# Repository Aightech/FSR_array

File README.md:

# FSR_array

This project implements a electronic skin using a FSR accelerometers arrays. 

The electronic board uses two multiplexers and two 16-channel ADCs to read the FSRs. The multiplexers are used to select the row or column of the FSRs array. The ADCs are used to read the FSRs values.
A teensy 4.1 is used to control the multiplexers and ADCs and to send the data to the computer.
The teensy 4.1 is connected to the computer using a USB cable or ethernet cable.
There are two modes of operation:
- **Single mode**: In this mode, you can connect a FSR array with up to 32x32 FSRs.
- **Dual mode**: In this mode, you can connect two FSR arrays with up to 16x16 FSRs each.

The sampling is around 400KHz/channel. So for a 16x16 FSR array, the sampling rate is around 400KHz/256 = 1562.5Hz.

The project contains a C++/matlab/python code demonstrating how to communicate with the teensy 4.1 and read the FSRs values.

### Submodules dependencies
#### libraries
- [built_lsl](lib/built_lsl/README.md)
- [com_client](lib/com_client/README.md)

# Building source code

To build the project run:
```bash
cd FSR_array
mkdir build && cd build
cmake .. && make
```

# Demonstration app

When the project have been built, you can run:
```bash
./FSR_array -h
```
to get the demonstration app usage.

# Example
Open the  file to get an example how to use the lib.

# Contributing
See [CONTRIBUTING.md](CONTRIBUTING.md) for details on our code of conduct, and the process for submitting pull requests to us.

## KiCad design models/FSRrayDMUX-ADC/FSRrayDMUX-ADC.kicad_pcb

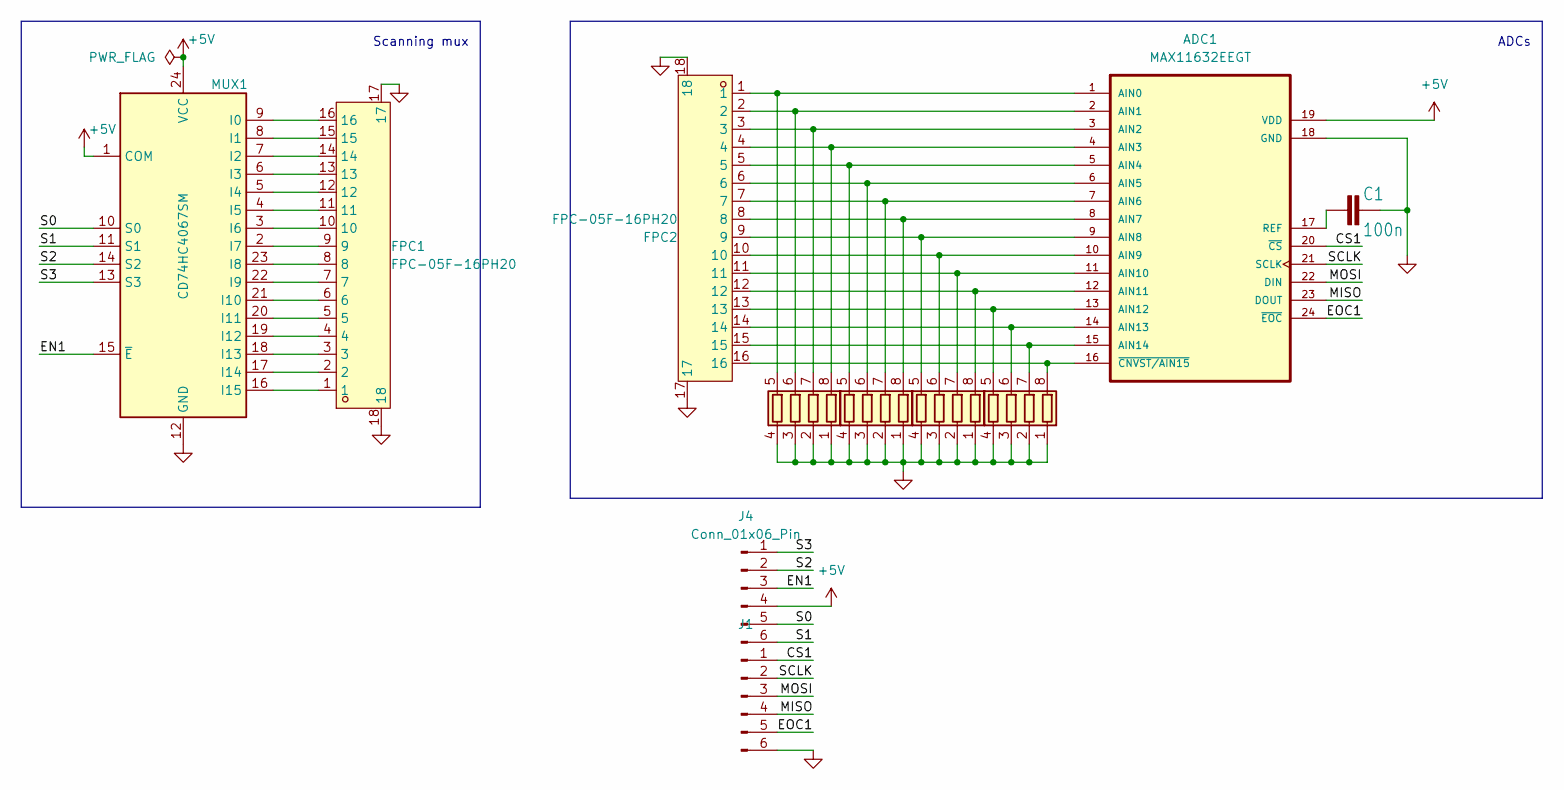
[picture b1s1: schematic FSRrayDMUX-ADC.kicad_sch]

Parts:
ADC1: MAX11632EEGT
C1: 100n; C_0402_1005Metric
FPC1, FPC2: FPC-05F-16PH20; FPC-SMD_16P-P0.50_FPC-05F-16PH20; LCSC Part C2856801
J1, J4: Conn_01x06_Pin; PinSocket_1x06_P2.54mm_Vertical
MUX1: CD74HC4067SM; SSOP-24_5.3x8.2mm_P0.65mm
RN1, RN2, RN3, RN4: R_Pack04; R_Array_Convex_4x0402

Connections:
+5V: ADC1.19 (VDD), J4.4, MUX1.1 (COM), MUX1.24 (VCC)
/CS1: ADC1.20 (~CS), J1.1
/EN1: J4.3, MUX1.15 (~E)
/EOC1: ADC1.24 (~EOC), J1.5
/MISO: ADC1.23 (DOUT), J1.4
/MOSI: ADC1.22 (DIN), J1.3
/S0: J4.5, MUX1.10 (S0)
/S1: J4.6, MUX1.11 (S1)
/S2: J4.2, MUX1.14 (S2)
/S3: J4.1, MUX1.13 (S3)
/SCLK: ADC1.21 (SCLK), J1.2
GND: ADC1.18 (GND), C1.2, FPC1.17, FPC1.18, FPC2.17, FPC2.18, J1.6, MUX1.12 (GND), RN1.1 (R1.1), RN1.2 (R2.1), RN1.3 (R3.1), RN1.4 (R4.1), RN2.1 (R1.1), RN2.2 (R2.1), RN2.3 (R3.1), RN2.4 (R4.1), RN3.1 (R1.1), RN3.2 (R2.1), RN3.3 (R3.1), RN3.4 (R4.1), RN4.1 (R1.1), RN4.2 (R2.1), RN4.3 (R3.1), RN4.4 (R4.1)
unnamed: ADC1.1 (AIN0), FPC2.1, RN1.5 (R4.2)
unnamed: ADC1.2 (AIN1), FPC2.2, RN1.6 (R3.2)
unnamed: ADC1.3 (AIN2), FPC2.3, RN1.7 (R2.2)
unnamed: ADC1.4 (AIN3), FPC2.4, RN1.8 (R1.2)
unnamed: ADC1.5 (AIN4), FPC2.5, RN2.5 (R4.2)
unnamed: ADC1.6 (AIN5), FPC2.6, RN2.6 (R3.2)
unnamed: ADC1.7 (AIN6), FPC2.7, RN2.7 (R2.2)
unnamed: ADC1.8 (AIN7), FPC2.8, RN2.8 (R1.2)
unnamed: ADC1.9 (AIN8), FPC2.9, RN3.5 (R4.2)
unnamed: ADC1.10 (AIN9), FPC2.10, RN3.6 (R3.2)
unnamed: ADC1.11 (AIN10), FPC2.11, RN3.7 (R2.2)
unnamed: ADC1.12 (AIN11), FPC2.12, RN3.8 (R1.2)
unnamed: ADC1.13 (AIN12), FPC2.13, RN4.5 (R4.2)
unnamed: ADC1.14 (AIN13), FPC2.14, RN4.6 (R3.2)
unnamed: ADC1.15 (AIN14), FPC2.15, RN4.7 (R2.2)
unnamed: ADC1.17 (REF), C1.1
unnamed: ADC1.16 (~CNVST/AIN15), FPC2.16, RN4.8 (R1.2)
unnamed: FPC1.16, MUX1.9 (I0)
unnamed: FPC1.15, MUX1.8 (I1)
unnamed: FPC1.14, MUX1.7 (I2)
unnamed: FPC1.13, MUX1.6 (I3)
unnamed: FPC1.12, MUX1.5 (I4)
unnamed: FPC1.11, MUX1.4 (I5)
unnamed: FPC1.10, MUX1.3 (I6)
unnamed: FPC1.9, MUX1.2 (I7)
unnamed: FPC1.8, MUX1.23 (I8)
unnamed: FPC1.7, MUX1.22 (I9)
unnamed: FPC1.6, MUX1.21 (I10)
unnamed: FPC1.5, MUX1.20 (I11)
unnamed: FPC1.4, MUX1.19 (I12)
unnamed: FPC1.3, MUX1.18 (I13)
unnamed: FPC1.2, MUX1.17 (I14)
unnamed: FPC1.1, MUX1.16 (I15)

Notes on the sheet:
ADCs
Scanning mux

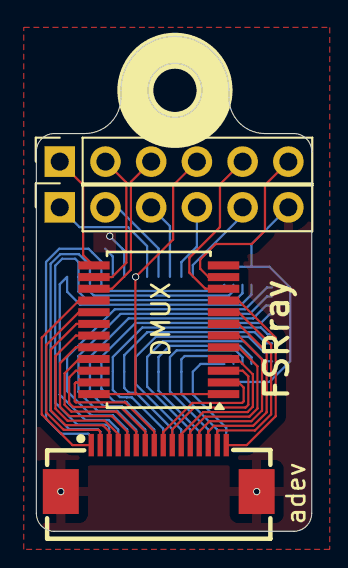
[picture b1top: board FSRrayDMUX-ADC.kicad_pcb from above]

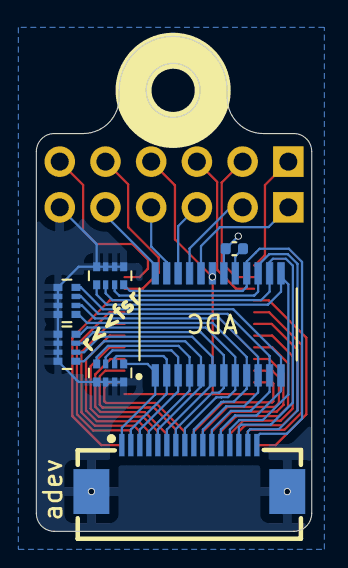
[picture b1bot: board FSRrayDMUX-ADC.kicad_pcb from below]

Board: 4 copper layers, 15.3 x 27.5 mm, 11 parts (7 on the bottom side), 45 nets.

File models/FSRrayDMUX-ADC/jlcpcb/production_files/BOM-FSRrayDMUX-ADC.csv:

Comment,Designator,Footprint,LCSC,Quantity
FPC-05F-16PH20,"FPC1,FPC2",FPC-SMD_16P-P0.50_FPC-05F-16PH20,C2856801,2
Conn_01x06_Pin,J1,PinSocket_1x06_P2.54mm_Vertical,,1
CD74HC4067SM,MUX1,SSOP-24_5.3x8.2mm_P0.65mm,,1
Conn_01x06_Pin,J4,PinSocket_1x06_P2.54mm_Vertical,,1
R_Pack04,RN4,R_Array_Convex_4x0402,,1
R_Pack04,RN2,R_Array_Convex_4x0402,,1
R_Pack04,RN1,R_Array_Convex_4x0402,,1
100n,C1,C_0402_1005Metric,,1
R_Pack04,RN3,R_Array_Convex_4x0402,,1
MAX11632EEGT,ADC1,MAX11632EEGT,,1

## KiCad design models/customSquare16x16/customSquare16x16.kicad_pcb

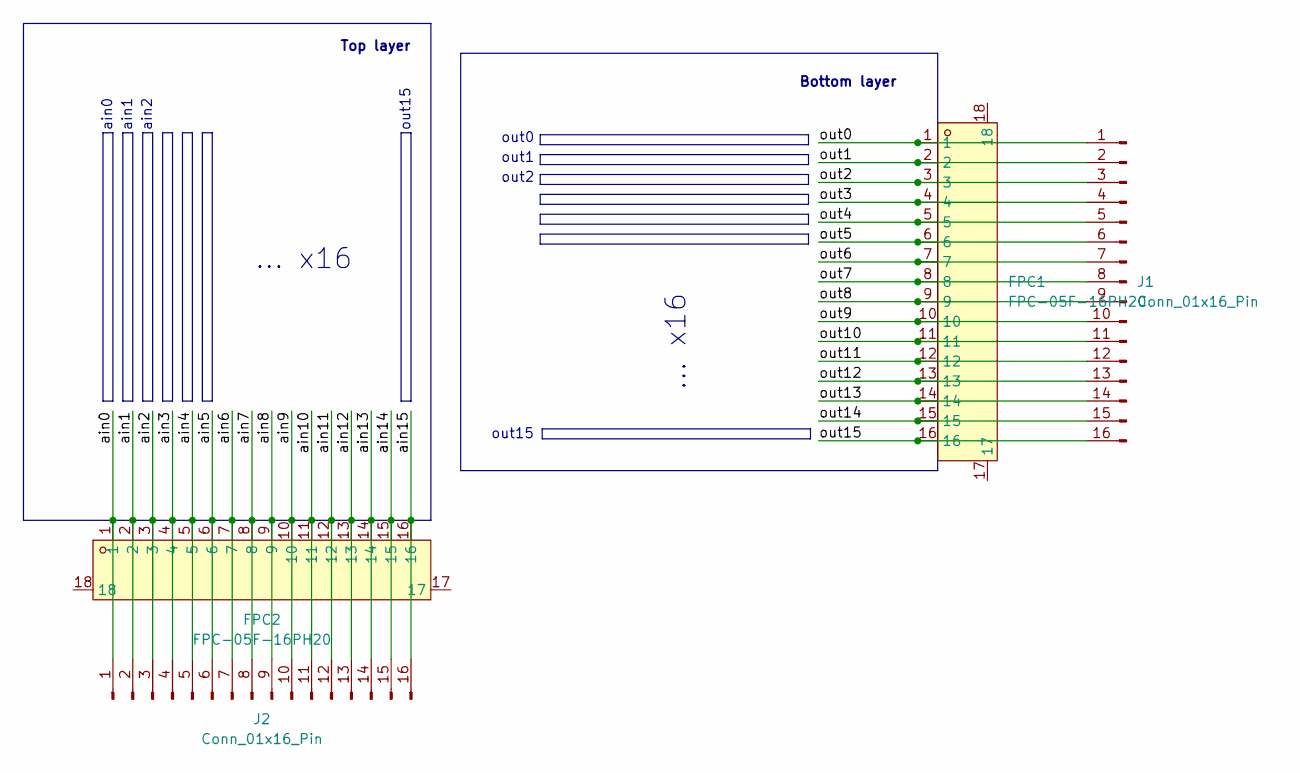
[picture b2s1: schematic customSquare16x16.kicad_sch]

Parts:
FPC1, FPC2: FPC-05F-16PH20; FPC-SMD_16P-P0.50_FPC-05F-16PH20; LCSC Part C2856801
J1, J2: Conn_01x16_Pin; PinSocket_1x16_P2.54mm_Vertical

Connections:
/ain0: FPC2.1, J2.1
/ain1: FPC2.2, J2.2
/ain2: FPC2.3, J2.3
/ain3: FPC2.4, J2.4
/ain4: FPC2.5, J2.5
/ain5: FPC2.6, J2.6
/ain6: FPC2.7, J2.7
/ain7: FPC2.8, J2.8
/ain8: FPC2.9, J2.9
/ain9: FPC2.10, J2.10
/ain10: FPC2.11, J2.11
/ain11: FPC2.12, J2.12
/ain12: FPC2.13, J2.13
/ain13: FPC2.14, J2.14
/ain14: FPC2.15, J2.15
/ain15: FPC2.16, J2.16
/out0: FPC1.1, J1.1
/out1: FPC1.2, J1.2
/out2: FPC1.3, J1.3
/out3: FPC1.4, J1.4
/out4: FPC1.5, J1.5
/out5: FPC1.6, J1.6
/out6: FPC1.7, J1.7
/out7: FPC1.8, J1.8
/out8: FPC1.9, J1.9
/out9: FPC1.10, J1.10
/out10: FPC1.11, J1.11
/out11: FPC1.12, J1.12
/out12: FPC1.13, J1.13
/out13: FPC1.14, J1.14
/out14: FPC1.15, J1.15
/out15: FPC1.16, J1.16

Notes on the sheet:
... x16
Bottom layer
ain0
out15
ain1
Top layer
ain2
out2
out0
out1

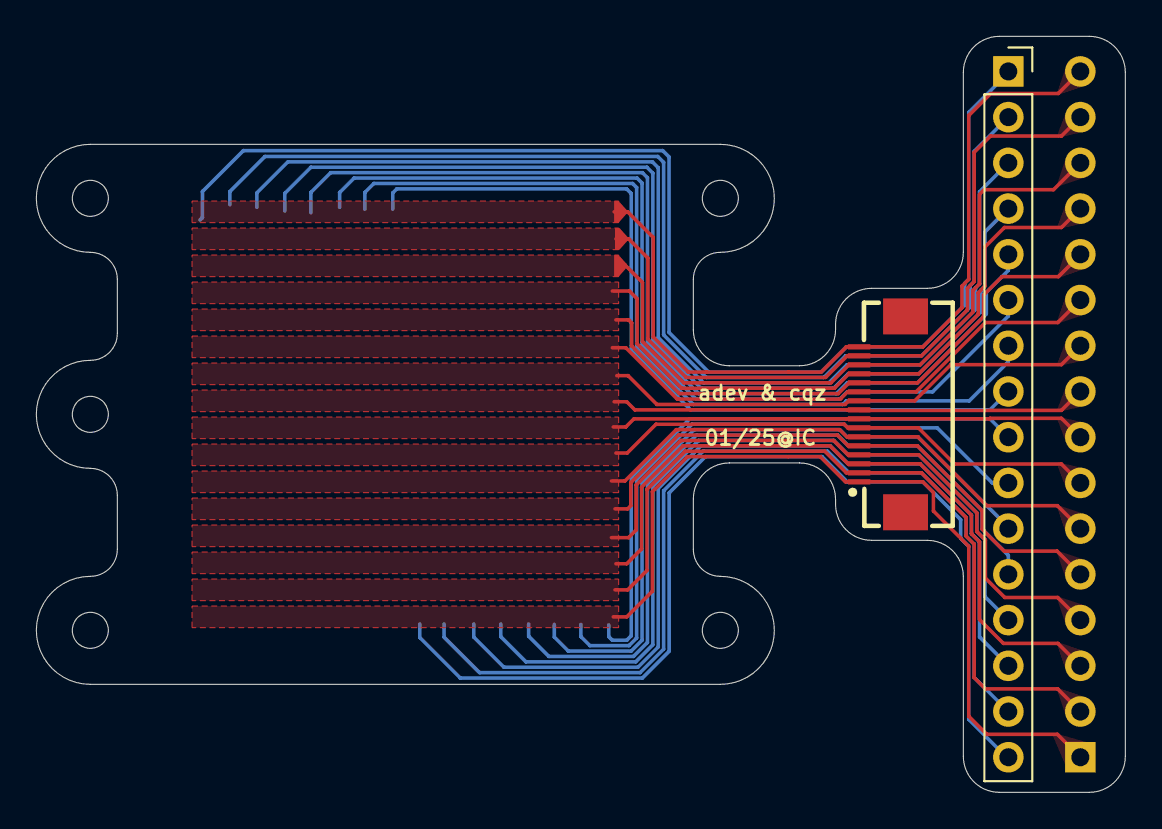
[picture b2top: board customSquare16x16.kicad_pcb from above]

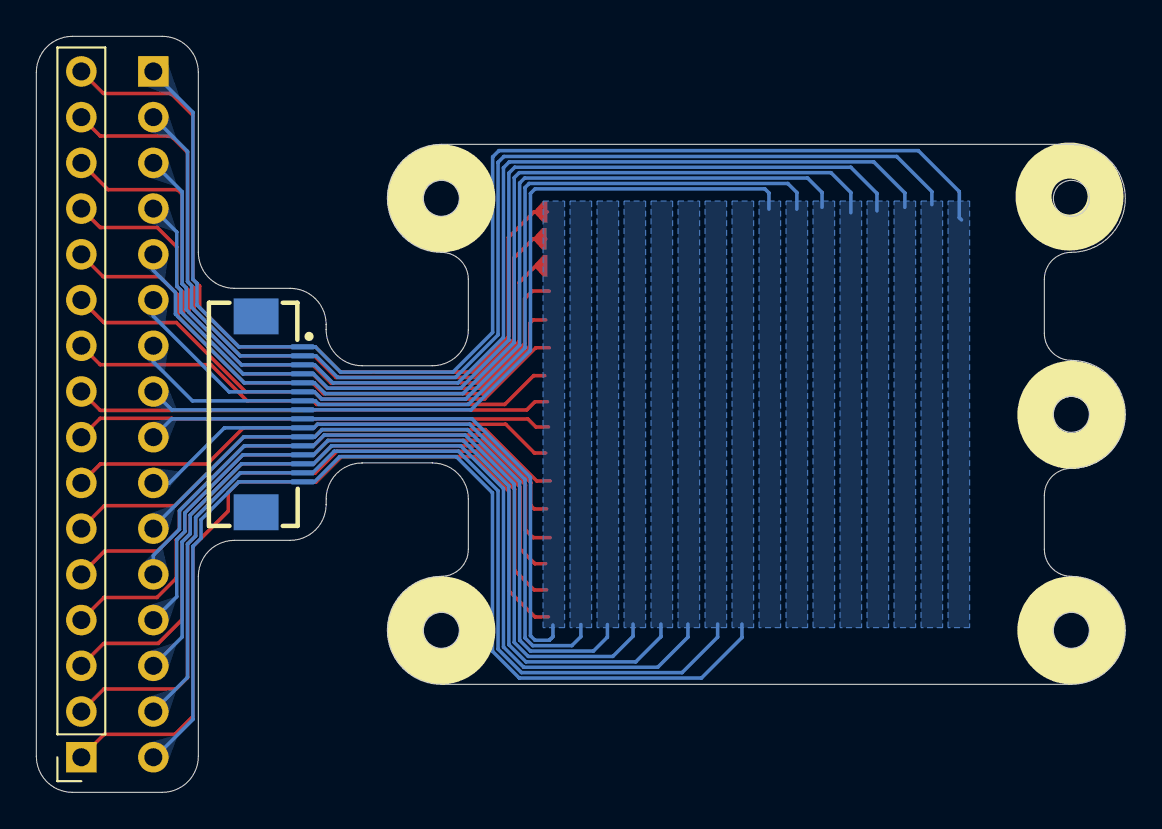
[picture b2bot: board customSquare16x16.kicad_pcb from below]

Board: 2 copper layers, 60.5 x 42.0 mm, 4 parts (2 on the bottom side), 32 nets.

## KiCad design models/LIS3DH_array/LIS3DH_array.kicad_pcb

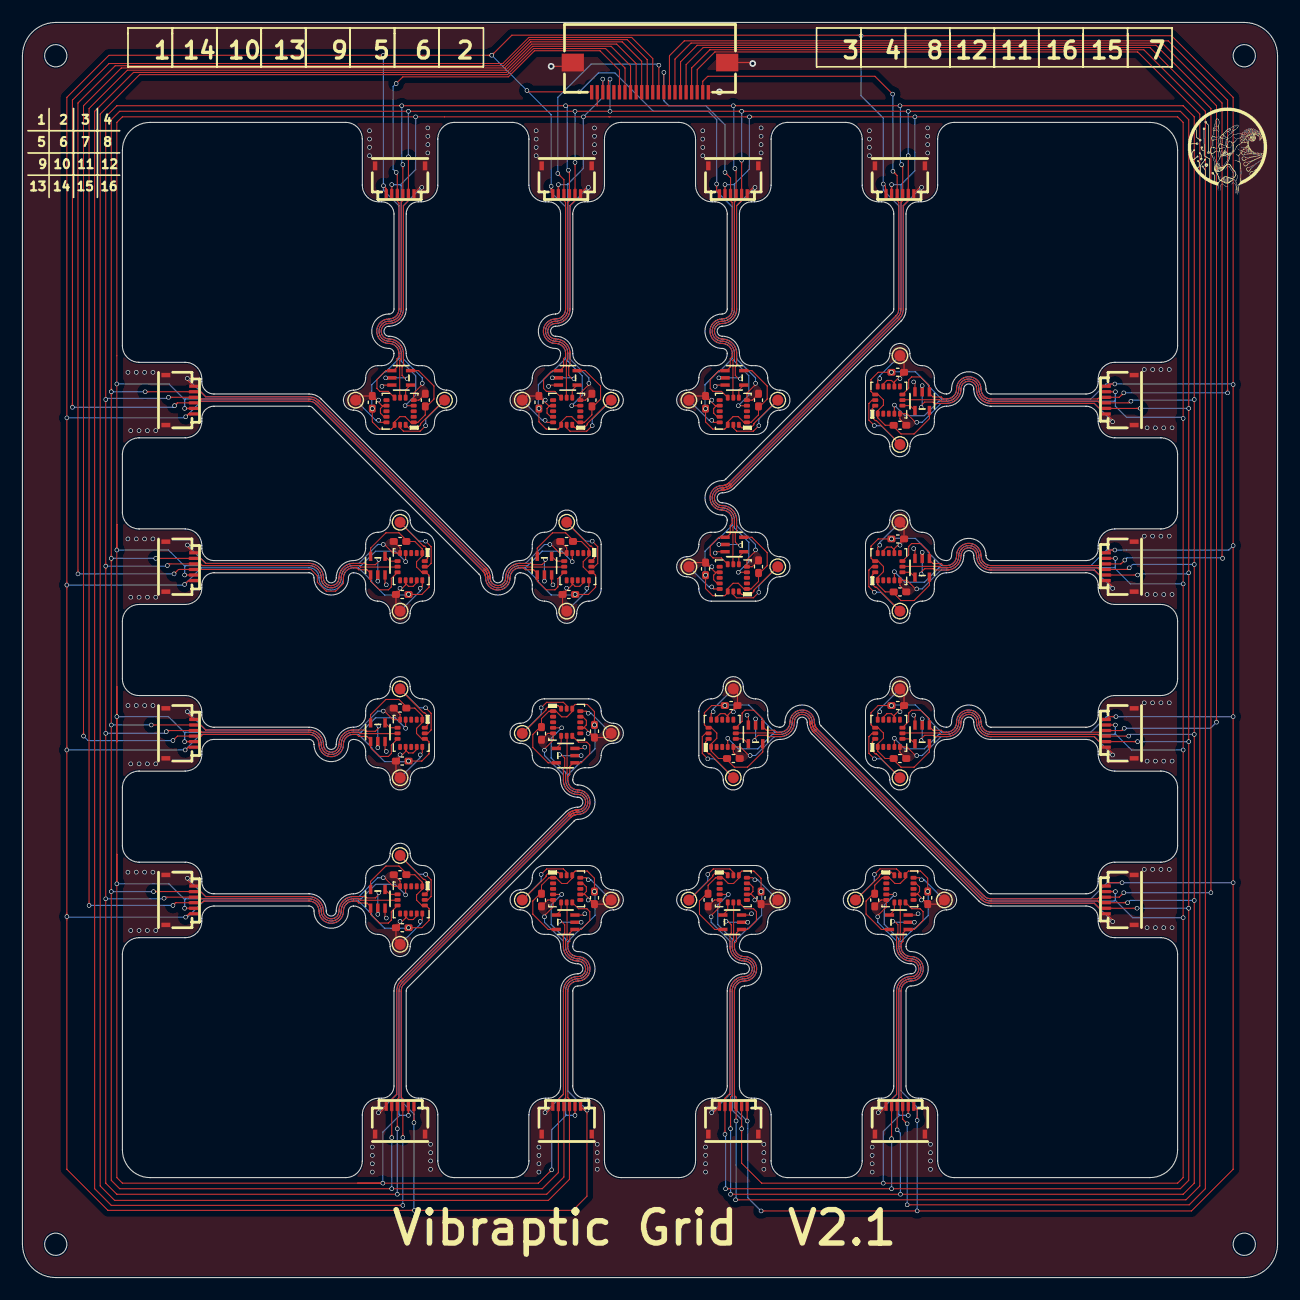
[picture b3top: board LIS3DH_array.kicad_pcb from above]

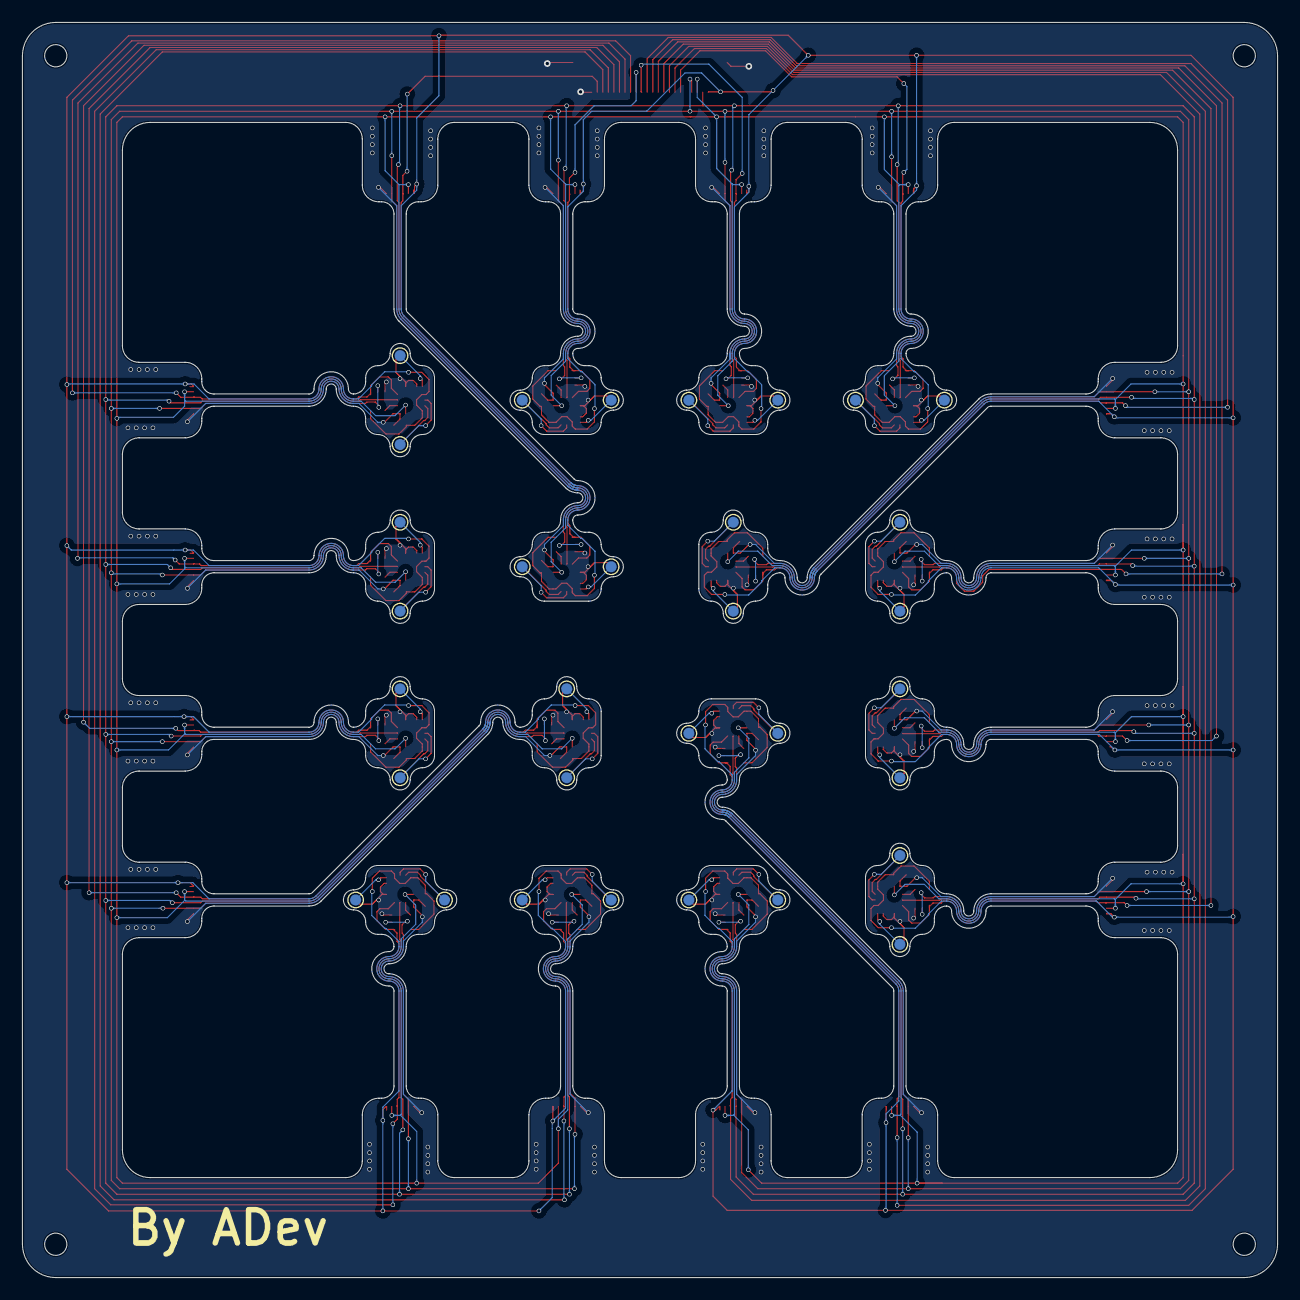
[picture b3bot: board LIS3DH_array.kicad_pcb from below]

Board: 2 copper layers, 113.0 x 113.0 mm, 145 parts (32 on the bottom side), 85 nets.

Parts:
C1, C3, C5, C7, C9, C11, C13, C15, C17, C19, C21, C23, C25, C27, C29, C31: 100n; C_0402_1005Metric_Pad0.74x0.62mm_HandSolder
C2, C4, C6, C8, C10, C12, C14, C16, C18, C20, C22, C24, C26, C28, C30, C32: 1u; C_0402_1005Metric_Pad0.74x0.62mm_HandSolder
FPC1, FPC2, FPC3, FPC4, FPC5, FPC6, FPC7, FPC8, FPC9, FPC10, FPC11, FPC12, FPC13, FPC14, FPC15, FPC16: HC-FPC-05-09-6RLTAG; FPC-SMD_6P-P0.50_HC-FPC-05-09-6RLTAG
FPC17: AFC01-S22FCA-00; FPC-SMD_P0.5-22P_FGS-XJ-H2.0
TP1, TP2, TP3, TP4, TP5, TP6, TP7, TP8, TP9, TP10, TP11, TP12, TP13, TP14, TP15, TP16, TP17, TP18, TP19, TP20, TP21, TP22, TP23, TP24, TP25, TP26, TP27, TP28, TP29, TP30, TP31, TP32, TP33, TP34, TP35, TP36, TP37, TP38, TP39, TP40, TP41, TP42, TP43, TP44, TP45, TP46, TP47, TP48, TP49, TP50, TP51, TP52, TP53, TP54, TP55, TP56, TP57, TP58, TP59, TP60, TP61, TP62, TP63, TP64: TestPoint; TestPoint_Pad_D1.0mm
U1, U2, U3, U4, U5, U6, U7, U8, U9, U10, U11, U12, U13, U14, U15, U16: LIS3DH; LGA-16_3x3mm_P0.5mm_LayoutBorder3x5y
U17, U18, U19, U20, U21, U22, U23, U24, U25, U26, U27, U28, U29, U30, U31, U32: SN74LVC1G32DCKR; SOT-353_L2.1-W1.3-P0.65-LS2.3-BR

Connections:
/LIS3DH_unit1/ADC1: TP1.1, U1.16 (ADC1)
/LIS3DH_unit1/ADC2: TP10.1, U1.15 (ADC2)
/LIS3DH_unit1/ADC3: TP19.1, U1.13 (ADC3)
/LIS3DH_unit2/ADC1: TP2.1, U2.16 (ADC1)
/LIS3DH_unit2/ADC2: TP11.1, U2.15 (ADC2)
/LIS3DH_unit2/ADC3: TP20.1, U2.13 (ADC3)
/LIS3DH_unit3/ADC1: TP3.1, U3.16 (ADC1)
/LIS3DH_unit3/ADC2: TP12.1, U3.15 (ADC2)
/LIS3DH_unit3/ADC3: TP21.1, U3.13 (ADC3)
/LIS3DH_unit4/ADC1: TP4.1, U4.16 (ADC1)
/LIS3DH_unit4/ADC2: TP13.1, U4.15 (ADC2)
/LIS3DH_unit4/ADC3: TP22.1, U4.13 (ADC3)
/LIS3DH_unit5/ADC1: TP5.1, U5.16 (ADC1)
/LIS3DH_unit5/ADC2: TP14.1, U5.15 (ADC2)
/LIS3DH_unit5/ADC3: TP23.1, U5.13 (ADC3)
/LIS3DH_unit6/ADC1: TP6.1, U6.16 (ADC1)
/LIS3DH_unit6/ADC2: TP15.1, U6.15 (ADC2)
/LIS3DH_unit6/ADC3: TP24.1, U6.13 (ADC3)
/LIS3DH_unit7/ADC1: TP7.1, U7.16 (ADC1)
/LIS3DH_unit7/ADC2: TP16.1, U7.15 (ADC2)
/LIS3DH_unit7/ADC3: TP25.1, U7.13 (ADC3)
/LIS3DH_unit8/ADC1: TP8.1, U8.16 (ADC1)
/LIS3DH_unit8/ADC2: TP17.1, U8.15 (ADC2)
/LIS3DH_unit8/ADC3: TP26.1, U8.13 (ADC3)
/LIS3DH_unit9/ADC1: TP9.1, U9.16 (ADC1)
/LIS3DH_unit9/ADC2: TP18.1, U9.15 (ADC2)
/LIS3DH_unit9/ADC3: TP27.1, U9.13 (ADC3)
/LIS3DH_unit10/ADC1: TP37.1, U10.16 (ADC1)
/LIS3DH_unit10/ADC2: TP38.1, U10.15 (ADC2)
/LIS3DH_unit10/ADC3: TP39.1, U10.13 (ADC3)
/LIS3DH_unit11/ADC1: TP41.1, U11.16 (ADC1)
/LIS3DH_unit11/ADC2: TP42.1, U11.15 (ADC2)
/LIS3DH_unit11/ADC3: TP43.1, U11.13 (ADC3)
/LIS3DH_unit12/ADC1: TP45.1, U12.16 (ADC1)
/LIS3DH_unit12/ADC2: TP46.1, U12.15 (ADC2)
/LIS3DH_unit12/ADC3: TP47.1, U12.13 (ADC3)
/LIS3DH_unit13/ADC1: TP49.1, U13.16 (ADC1)
/LIS3DH_unit13/ADC2: TP50.1, U13.15 (ADC2)
/LIS3DH_unit13/ADC3: TP51.1, U13.13 (ADC3)
/LIS3DH_unit14/ADC1: TP53.1, U14.16 (ADC1)
/LIS3DH_unit14/ADC2: TP54.1, U14.15 (ADC2)
/LIS3DH_unit14/ADC3: TP55.1, U14.13 (ADC3)
/LIS3DH_unit15/ADC1: TP57.1, U15.16 (ADC1)
/LIS3DH_unit15/ADC2: TP58.1, U15.15 (ADC2)
/LIS3DH_unit15/ADC3: TP59.1, U15.13 (ADC3)
/LIS3DH_unit16/ADC1: TP61.1, U16.16 (ADC1)
/LIS3DH_unit16/ADC2: TP62.1, U16.15 (ADC2)
/LIS3DH_unit16/ADC3: TP63.1, U16.13 (ADC3)
GND: C1.2, C2.2, C3.2, C4.2, C5.2, C6.2, C7.2, C8.2, C9.2, C10.2, C11.2, C12.2, C13.2, C14.2, C15.2, C16.2, C17.2, C18.2, C19.2, C20.2, C21.2, C22.2, C23.2, C24.2, C25.2, C26.2, C27.2, C28.2, C29.2, C30.2, C31.2, C32.2, FPC1.1, FPC1.7, FPC1.8, FPC2.1, FPC2.7, FPC2.8, FPC3.1, FPC3.7, FPC3.8, FPC4.1, FPC4.7, FPC4.8, FPC5.1, FPC5.7, FPC5.8, FPC6.1, FPC6.7, FPC6.8, FPC7.1, FPC7.7, FPC7.8, FPC8.1, FPC8.7, FPC8.8, FPC9.1, FPC9.7, FPC9.8, FPC10.1, FPC10.7, FPC10.8, FPC11.1, FPC11.7, FPC11.8, FPC12.1, FPC12.7, FPC12.8, FPC13.1, FPC13.7, FPC13.8, FPC14.1, FPC14.7, FPC14.8, FPC15.1, FPC15.7, FPC15.8, FPC16.1, FPC16.7, FPC16.8, FPC17.22, FPC17.23, FPC17.24, TP28.1, TP29.1, TP30.1, TP31.1, TP32.1, TP33.1, TP34.1, TP35.1, TP36.1, TP40.1, TP44.1, TP48.1, TP52.1, TP56.1, TP60.1, TP64.1, U1.5 (GND), U1.10 (RES), U1.12 (GND), U2.5 (GND), U2.10 (RES), U2.12 (GND), U3.5 (GND), U3.10 (RES), U3.12 (GND), U4.5 (GND), U4.10 (RES), U4.12 (GND), U5.5 (GND), U5.10 (RES), U5.12 (GND), U6.5 (GND), U6.10 (RES), U6.12 (GND), U7.5 (GND), U7.10 (RES), U7.12 (GND), U8.5 (GND), U8.10 (RES), U8.12 (GND), U9.5 (GND), U9.10 (RES), U9.12 (GND), U10.5 (GND), U10.10 (RES), U10.12 (GND), U11.5 (GND), U11.10 (RES), U11.12 (GND), U12.5 (GND), U12.10 (RES), U12.12 (GND), U13.5 (GND), U13.10 (RES), U13.12 (GND), U14.5 (GND), U14.10 (RES), U14.12 (GND), U15.5 (GND), U15.10 (RES), U15.12 (GND), U16.5 (GND), U16.10 (RES), U16.12 (GND), U17.3 (GND), U18.3 (GND), U19.3 (GND), U20.3 (GND), U21.3 (GND), U22.3 (GND), U23.3 (GND), U24.3 (GND), U25.3 (GND), U26.3 (GND), U27.3 (GND), U28.3 (GND), U29.3 (GND), U30.3 (GND), U31.3 (GND), U32.3 (GND)
unnamed: U1.6 (SDA/SDI/SDO), U17.4 (Y)
unnamed: U10.6 (SDA/SDI/SDO), U26.4 (Y)
unnamed: U11.6 (SDA/SDI/SDO), U27.4 (Y)
unnamed: U12.6 (SDA/SDI/SDO), U28.4 (Y)
unnamed: U13.6 (SDA/SDI/SDO), U29.4 (Y)
unnamed: U14.6 (SDA/SDI/SDO), U30.4 (Y)
unnamed: U15.6 (SDA/SDI/SDO), U31.4 (Y)
unnamed: U16.6 (SDA/SDI/SDO), U32.4 (Y)
unnamed: U2.6 (SDA/SDI/SDO), U18.4 (Y)
unnamed: U3.6 (SDA/SDI/SDO), U19.4 (Y)
unnamed: U4.6 (SDA/SDI/SDO), U20.4 (Y)
unnamed: U5.6 (SDA/SDI/SDO), U21.4 (Y)
unnamed: U6.6 (SDA/SDI/SDO), U22.4 (Y)
unnamed: U7.6 (SDA/SDI/SDO), U23.4 (Y)
unnamed: U8.6 (SDA/SDI/SDO), U24.4 (Y)
unnamed: U9.6 (SDA/SDI/SDO), U25.4 (Y)
SDI: FPC1.2, FPC2.2, FPC3.2, FPC4.2, FPC5.2, FPC6.2, FPC7.2, FPC8.2, FPC9.2, FPC10.2, FPC11.2, FPC12.2, FPC13.2, FPC14.2, FPC15.2, FPC16.2, FPC17.4, U17.2 (B), U18.2 (B), U19.2 (B), U20.2 (B), U21.2 (B), U22.2 (B), U23.2 (B), U24.2 (B), U25.2 (B), U26.2 (B), U27.2 (B), U28.2 (B), U29.2 (B), U30.2 (B), U31.2 (B), U32.2 (B)
SDO: FPC1.3, FPC2.3, FPC3.3, FPC4.3, FPC5.3, FPC6.3, FPC7.3, FPC8.3, FPC9.3, FPC10.3, FPC11.3, FPC12.3, FPC13.3, FPC14.3, FPC15.3, FPC16.3, FPC17.2, U1.7 (SDO/SA0), U2.7 (SDO/SA0), U3.7 (SDO/SA0), U4.7 (SDO/SA0), U5.7 (SDO/SA0), U6.7 (SDO/SA0), U7.7 (SDO/SA0), U8.7 (SDO/SA0), U9.7 (SDO/SA0), U10.7 (SDO/SA0), U11.7 (SDO/SA0), U12.7 (SDO/SA0), U13.7 (SDO/SA0), U14.7 (SDO/SA0), U15.7 (SDO/SA0), U16.7 (SDO/SA0)
Sclk: FPC1.5, FPC2.5, FPC3.5, FPC4.5, FPC5.5, FPC6.5, FPC7.5, FPC8.5, FPC9.5, FPC10.5, FPC11.5, FPC12.5, FPC13.5, FPC14.5, FPC15.5, FPC16.5, FPC17.3, U1.4 (SCL/SPC), U2.4 (SCL/SPC), U3.4 (SCL/SPC), U4.4 (SCL/SPC), U5.4 (SCL/SPC), U6.4 (SCL/SPC), U7.4 (SCL/SPC), U8.4 (SCL/SPC), U9.4 (SCL/SPC), U10.4 (SCL/SPC), U11.4 (SCL/SPC), U12.4 (SCL/SPC), U13.4 (SCL/SPC), U14.4 (SCL/SPC), U15.4 (SCL/SPC), U16.4 (SCL/SPC)
VDD: C1.1, C2.1, C3.1, C4.1, C5.1, C6.1, C7.1, C8.1, C9.1, C10.1, C11.1, C12.1, C13.1, C14.1, C15.1, C16.1, C17.1, C18.1, C19.1, C20.1, C21.1, C22.1, C23.1, C24.1, C25.1, C26.1, C27.1, C28.1, C29.1, C30.1, C31.1, C32.1, FPC1.6, FPC2.6, FPC3.6, FPC4.6, FPC5.6, FPC6.6, FPC7.6, FPC8.6, FPC9.6, FPC10.6, FPC11.6, FPC12.6, FPC13.6, FPC14.6, FPC15.6, FPC16.6, FPC17.1, U1.1 (VDD_IO), U1.14 (VDD), U2.1 (VDD_IO), U2.14 (VDD), U3.1 (VDD_IO), U3.14 (VDD), U4.1 (VDD_IO), U4.14 (VDD), U5.1 (VDD_IO), U5.14 (VDD), U6.1 (VDD_IO), U6.14 (VDD), U7.1 (VDD_IO), U7.14 (VDD), U8.1 (VDD_IO), U8.14 (VDD), U9.1 (VDD_IO), U9.14 (VDD), U10.1 (VDD_IO), U10.14 (VDD), U11.1 (VDD_IO), U11.14 (VDD), U12.1 (VDD_IO), U12.14 (VDD), U13.1 (VDD_IO), U13.14 (VDD), U14.1 (VDD_IO), U14.14 (VDD), U15.1 (VDD_IO), U15.14 (VDD), U16.1 (VDD_IO), U16.14 (VDD), U17.5 (VCC), U18.5 (VCC), U19.5 (VCC), U20.5 (VCC), U21.5 (VCC), U22.5 (VCC), U23.5 (VCC), U24.5 (VCC), U25.5 (VCC), U26.5 (VCC), U27.5 (VCC), U28.5 (VCC), U29.5 (VCC), U30.5 (VCC), U31.5 (VCC), U32.5 (VCC)
nCS_1: FPC1.4, FPC17.6, U1.8 (CS), U17.1 (A)
nCS_2: FPC2.4, FPC17.13, U2.8 (CS), U18.1 (A)
nCS_3: FPC3.4, FPC17.14, U3.8 (CS), U19.1 (A)
nCS_4: FPC4.4, FPC17.15, U4.8 (CS), U20.1 (A)
nCS_5: FPC5.4, FPC17.11, U5.8 (CS), U21.1 (A)
nCS_6: FPC6.4, FPC17.12, U6.8 (CS), U22.1 (A)
nCS_7: FPC7.4, FPC17.21, U7.8 (CS), U23.1 (A)
nCS_8: FPC8.4, FPC17.16, U8.8 (CS), U24.1 (A)
nCS_9: FPC9.4, FPC17.10, U9.8 (CS), U25.1 (A)
nCS_10: FPC10.4, FPC17.8, U10.8 (CS), U26.1 (A)
nCS_11: FPC11.4, FPC17.18, U11.8 (CS), U27.1 (A)
nCS_12: FPC12.4, FPC17.17, U12.8 (CS), U28.1 (A)
nCS_13: FPC13.4, FPC17.9, U13.8 (CS), U29.1 (A)
nCS_14: FPC14.4, FPC17.7, U14.8 (CS), U30.1 (A)
nCS_15: FPC15.4, FPC17.20, U15.8 (CS), U31.1 (A)
nCS_16: FPC16.4, FPC17.19, U16.8 (CS), U32.1 (A)

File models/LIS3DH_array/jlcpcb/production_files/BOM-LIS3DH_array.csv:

Comment,Designator,Footprint,LCSC
LIS3DH,"U1,U10,U11,U12,U13,U14,U15,U16,U2,U3,U4,U5,U6,U7,U8,U9",LGA-16_3x3mm_P0.5mm_LayoutBorder3x5y,C15134
AFC01-S22FCA-00,FPC17,FPC-SMD_P0.5-22P_FGS-XJ-H2.0,C262668
1u,"C10,C12,C14,C16,C18,C2,C20,C22,C24,C26,C28,C30,C32,C4,C6,C8",C_0402_1005Metric_Pad0.74x0.62mm_HandSolder,C307413
100n,"C1,C11,C13,C15,C17,C19,C21,C23,C25,C27,C29,C3,C31,C5,C7,C9",C_0402_1005Metric_Pad0.74x0.62mm_HandSolder,C41851
HC-FPC-05-09-6RLTAG,"FPC1,FPC10,FPC11,FPC12,FPC13,FPC14,FPC15,FPC16,FPC2,FPC3,FPC4,FPC5,FPC6,FPC7,FPC8,FPC9",FPC-SMD_6P-P0.50_HC-FPC-05-09-6RLTAG,C5213748
SN74LVC1G32DCKR,"U17,U18,U19,U20,U21,U22,U23,U24,U25,U26,U27,U28,U29,U30,U31,U32",SOT-353_L2.1-W1.3-P0.65-LS2.3-BR,C7840

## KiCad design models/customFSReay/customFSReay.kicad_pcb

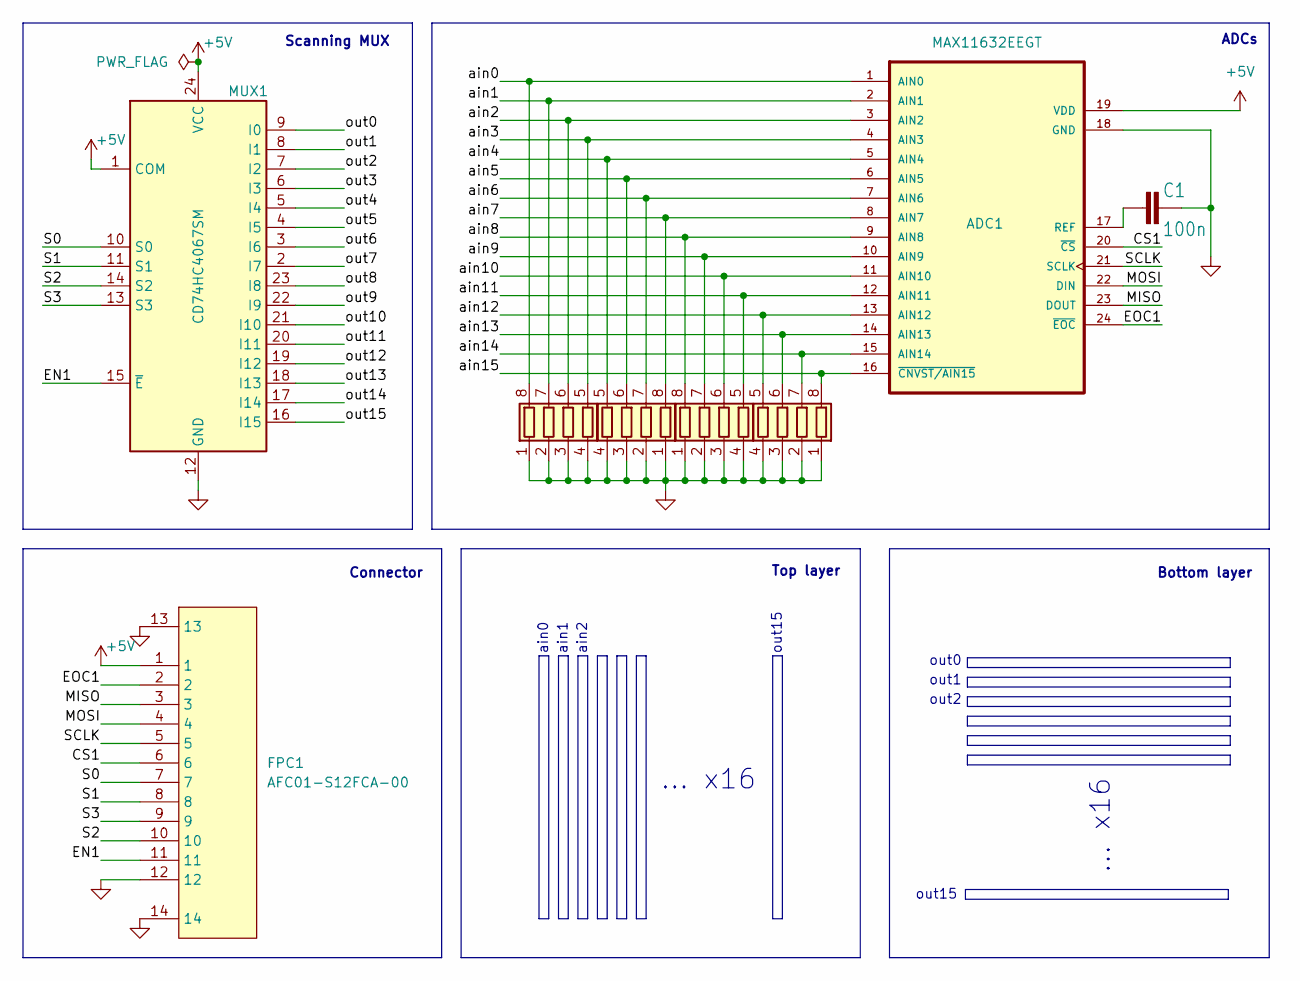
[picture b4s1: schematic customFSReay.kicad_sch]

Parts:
ADC1: MAX11632EEGT
C1: 100n; C0603
FPC1: AFC01-S12FCA-00; FPC-SMD_AFC01-S12FCA-00; LCSC Part C262661
MUX1: CD74HC4067SM; SSOP-24_5.3x8.2mm_P0.65mm
RN1, RN2, RN3, RN4: R_Pack04; R_Array_Convex_4x0402

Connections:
+5V: ADC1.19 (VDD), FPC1.1, MUX1.1 (COM), MUX1.24 (VCC)
/CS1: ADC1.20 (~CS), FPC1.6
/EN1: FPC1.11, MUX1.15 (~E)
/EOC1: ADC1.24 (~EOC), FPC1.2
/MISO: ADC1.23 (DOUT), FPC1.3
/MOSI: ADC1.22 (DIN), FPC1.4
/S0: FPC1.7, MUX1.10 (S0)
/S1: FPC1.8, MUX1.11 (S1)
/S2: FPC1.10, MUX1.14 (S2)
/S3: FPC1.9, MUX1.13 (S3)
/SCLK: ADC1.21 (SCLK), FPC1.5
/ain0: ADC1.1 (AIN0), RN1.8 (R1.2)
/ain1: ADC1.2 (AIN1), RN1.7 (R2.2)
/ain2: ADC1.3 (AIN2), RN1.6 (R3.2)
/ain3: ADC1.4 (AIN3), RN1.5 (R4.2)
/ain4: ADC1.5 (AIN4), RN2.5 (R4.2)
/ain5: ADC1.6 (AIN5), RN2.6 (R3.2)
/ain6: ADC1.7 (AIN6), RN2.7 (R2.2)
/ain7: ADC1.8 (AIN7), RN2.8 (R1.2)
/ain8: ADC1.9 (AIN8), RN3.8 (R1.2)
/ain9: ADC1.10 (AIN9), RN3.7 (R2.2)
/ain10: ADC1.11 (AIN10), RN3.6 (R3.2)
/ain11: ADC1.12 (AIN11), RN3.5 (R4.2)
/ain12: ADC1.13 (AIN12), RN4.5 (R4.2)
/ain13: ADC1.14 (AIN13), RN4.6 (R3.2)
/ain14: ADC1.15 (AIN14), RN4.7 (R2.2)
/ain15: ADC1.16 (~CNVST/AIN15), RN4.8 (R1.2)
/out0: MUX1.9 (I0)
/out1: MUX1.8 (I1)
/out2: MUX1.7 (I2)
/out3: MUX1.6 (I3)
/out4: MUX1.5 (I4)
/out5: MUX1.4 (I5)
/out6: MUX1.3 (I6)
/out7: MUX1.2 (I7)
/out8: MUX1.23 (I8)
/out9: MUX1.22 (I9)
/out10: MUX1.21 (I10)
/out11: MUX1.20 (I11)
/out12: MUX1.19 (I12)
/out13: MUX1.18 (I13)
/out14: MUX1.17 (I14)
/out15: MUX1.16 (I15)
GND: ADC1.18 (GND), C1.2, FPC1.12, FPC1.13, FPC1.14, MUX1.12 (GND), RN1.1 (R1.1), RN1.2 (R2.1), RN1.3 (R3.1), RN1.4 (R4.1), RN2.1 (R1.1), RN2.2 (R2.1), RN2.3 (R3.1), RN2.4 (R4.1), RN3.1 (R1.1), RN3.2 (R2.1), RN3.3 (R3.1), RN3.4 (R4.1), RN4.1 (R1.1), RN4.2 (R2.1), RN4.3 (R3.1), RN4.4 (R4.1)
unnamed: ADC1.17 (REF), C1.1

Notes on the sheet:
... x16
Bottom layer
ain0
out15
ain1
ADCs
Top layer
ain2
out2
out0
Scanning MUX
out1
Connector

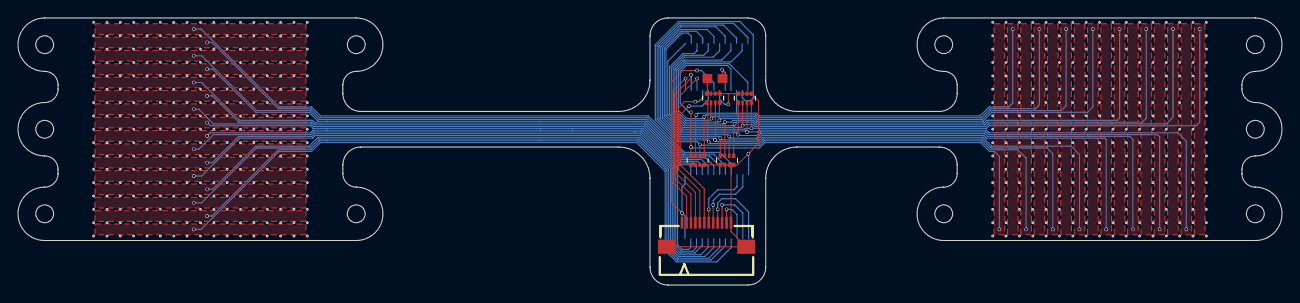
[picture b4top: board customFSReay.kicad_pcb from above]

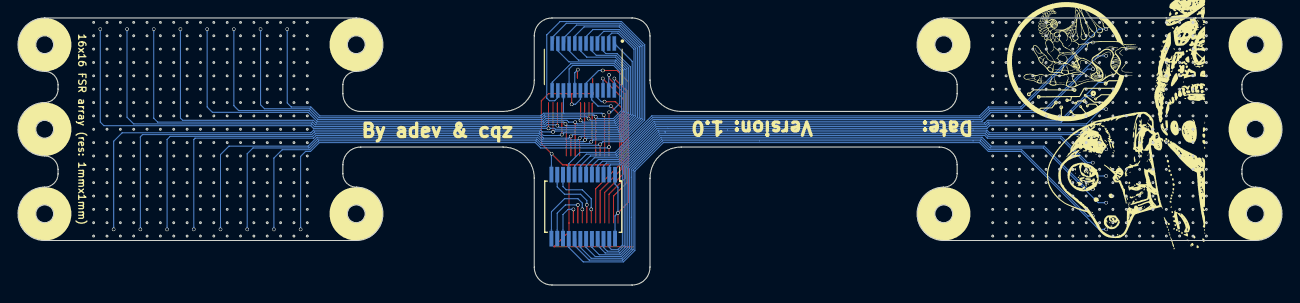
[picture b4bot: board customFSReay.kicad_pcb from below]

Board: 2 copper layers, 142.0 x 30.0 mm, 8 parts (2 on the bottom side), 29 nets.

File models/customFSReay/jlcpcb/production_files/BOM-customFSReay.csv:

Comment,Designator,Footprint,LCSC
AFC01-S12FCA-00,FPC1,FPC-SMD_AFC01-S12FCA-00,C262661
R_Pack04,RN1,R_Array_Convex_4x0402,
R_Pack04,RN4,R_Array_Convex_4x0402,
100n,C1,C0603,
R_Pack04,RN2,R_Array_Convex_4x0402,
R_Pack04,RN3,R_Array_Convex_4x0402,
CD74HC4067SM,MUX1,SSOP-24_5.3x8.2mm_P0.65mm,
MAX11632EEGT,ADC1,MAX11632EEGT,

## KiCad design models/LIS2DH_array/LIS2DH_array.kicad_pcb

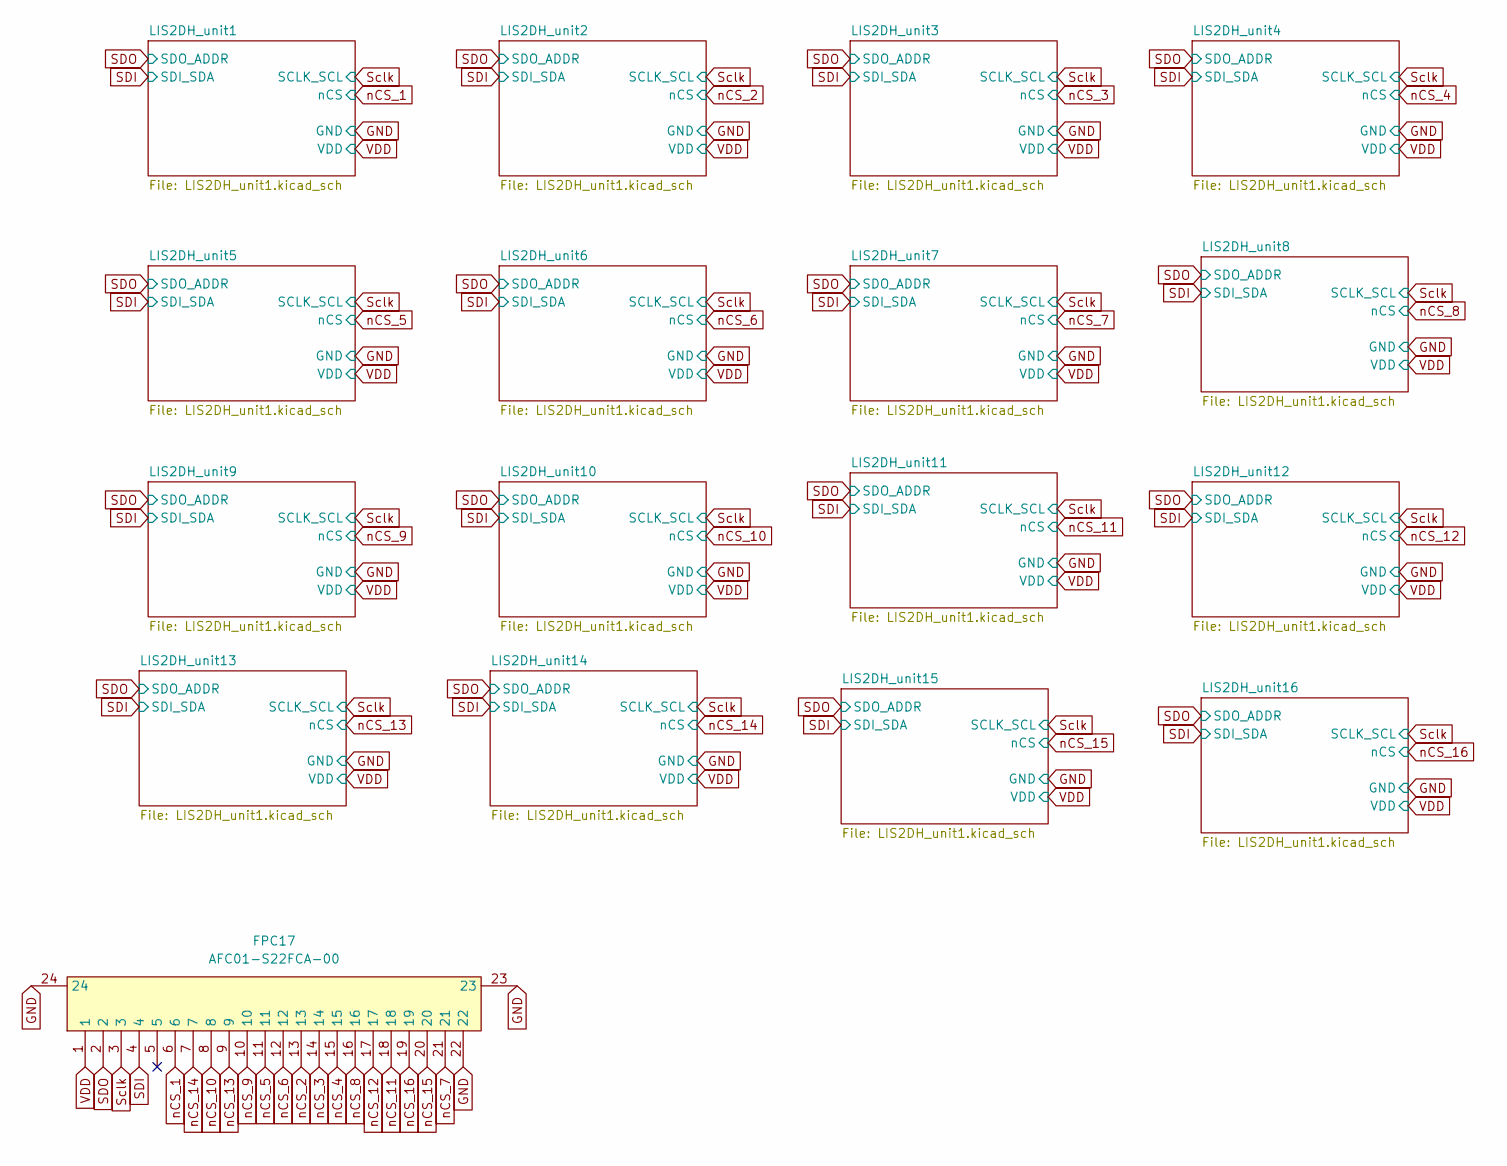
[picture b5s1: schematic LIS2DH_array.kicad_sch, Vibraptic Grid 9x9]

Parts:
FPC17: AFC01-S22FCA-00; FPC-SMD_P0.5-22P_FGS-XJ-H2.0; LCSC Part C262668

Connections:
GND: FPC17.22, FPC17.23, FPC17.24; also elsewhere on the board
SDI: FPC17.4; also elsewhere on the board
SDO: FPC17.2; also elsewhere on the board
Sclk: FPC17.3; also elsewhere on the board
VDD: FPC17.1; also elsewhere on the board
nCS_1: FPC17.6; also elsewhere on the board
nCS_2: FPC17.13; also elsewhere on the board
nCS_3: FPC17.14; also elsewhere on the board
nCS_4: FPC17.15; also elsewhere on the board
nCS_5: FPC17.11; also elsewhere on the board
nCS_6: FPC17.12; also elsewhere on the board
nCS_7: FPC17.21; also elsewhere on the board
nCS_8: FPC17.16; also elsewhere on the board
nCS_9: FPC17.10; also elsewhere on the board
nCS_10: FPC17.8; also elsewhere on the board
nCS_11: FPC17.18; also elsewhere on the board
nCS_12: FPC17.17; also elsewhere on the board
nCS_13: FPC17.9; also elsewhere on the board
nCS_14: FPC17.7; also elsewhere on the board
nCS_15: FPC17.20; also elsewhere on the board
nCS_16: FPC17.19; also elsewhere on the board
